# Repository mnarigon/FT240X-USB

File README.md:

## An FT240X-based parallel to USB converter

===== Description =====

This is an FT240X-based parallel to USB converter intended as an option for John Monahan's S-100 bus computer boards.

NOTE: These are the prototype files and I have not yet built and tested the prototype. I plan to update these files when that is complete. Quantity 5 boards was roughly $12 with tax and two-week shipping. Parts for 5 boards was roughly $50 with tax and one week shipping.

===== Design Files =====

The design files are in KiCad 10. The board fabrication parameters are 1.6mm, 2-layer, with 1 oz copper. There is a BOM in the documents folder.

===== Assembly Steps =====

  - Tin all the solder pads with the appropriate amount of solder.
  - Mount the front and back passives.
  - Mount the 24-SSOP transceiver.
  - Replace pins 1 and 9 on each 9-pin SMD connector header with pins from the THT connector header.
  - Mount the connector headers.
  - Mount the mini-USB connector.

The FT240X requires programming to enable the PWREN# functionality. For use in John's boards this is not required since John's designs do not use PWREN# and by default the signal is tri-stated.

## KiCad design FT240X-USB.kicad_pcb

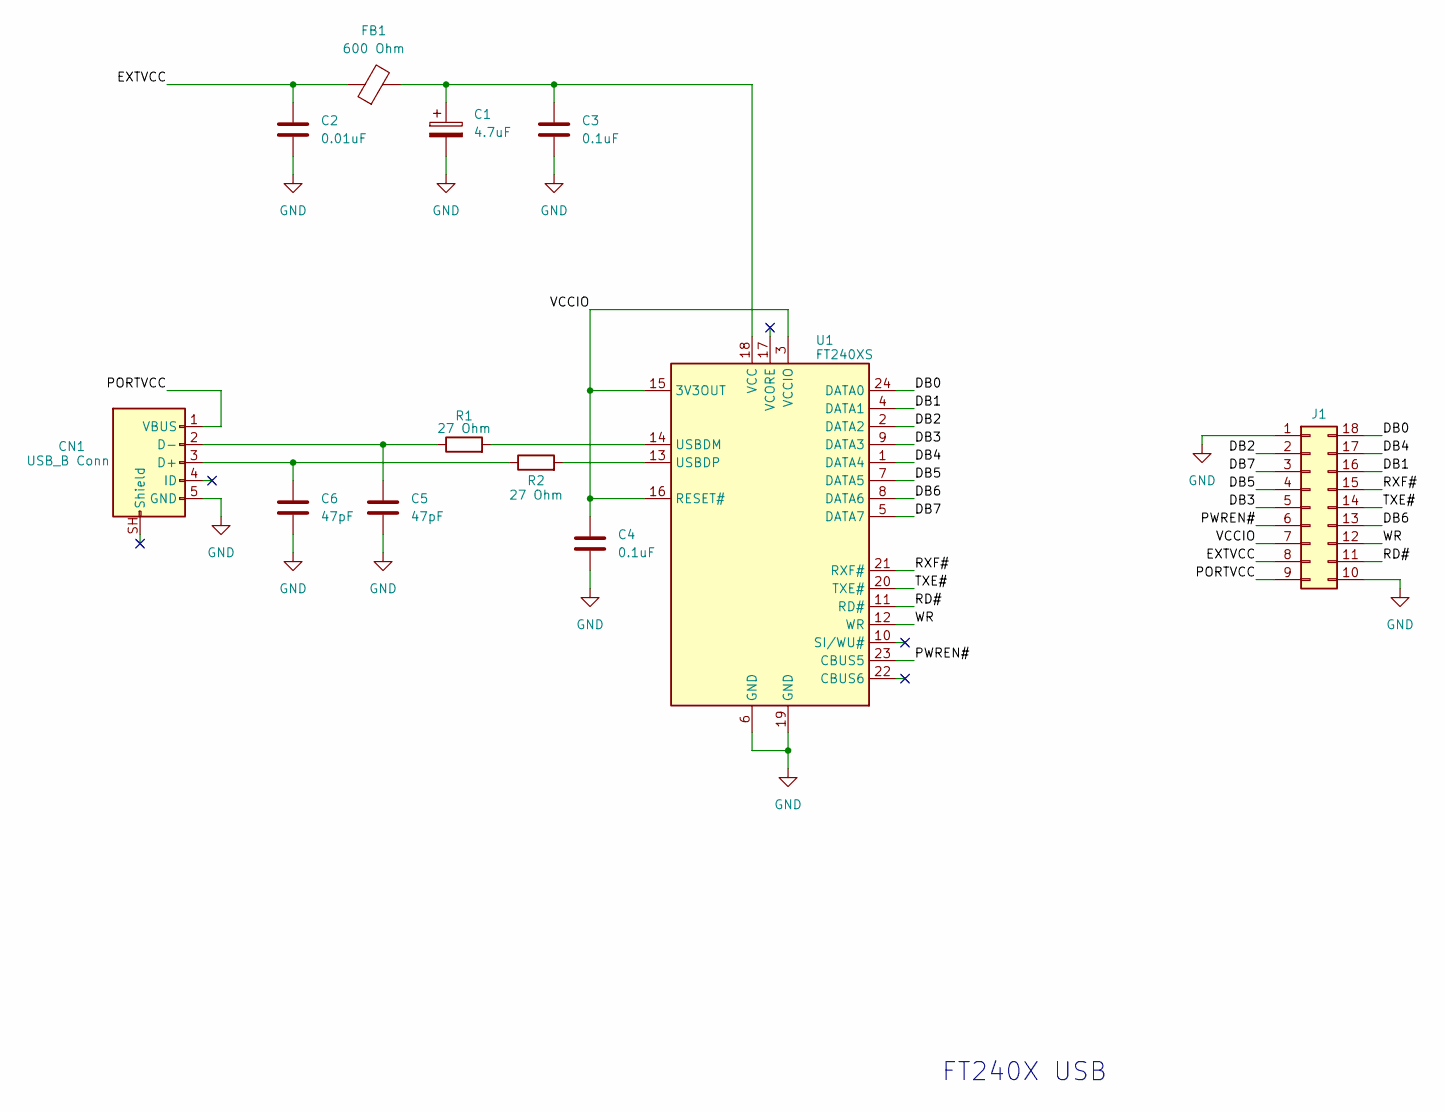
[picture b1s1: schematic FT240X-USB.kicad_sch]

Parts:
C1: 4.7uF; C_0805_2012Metric
C2: 0.01uF; C_0402_1005Metric
C3, C4: 0.1uF; C_0402_1005Metric
C5, C6: 47pF; C_0402_1005Metric
CN1: USB_B Conn; USB_Mini-B_TE_1734035_Horizontal
FB1: 600 Ohm; L_0805_2012Metric
J1: CustomPinHeader_02x09_P2.54mm_Hybrid
R1, R2: 27 Ohm; R_0402_1005Metric
U1: FT240XS; SSOP-24_3.9x8.7mm_P0.635mm

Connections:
/DB0: J1.18, U1.24 (DATA0)
/DB1: J1.16, U1.4 (DATA1)
/DB2: J1.2, U1.2 (DATA2)
/DB3: J1.5, U1.9 (DATA3)
/DB4: J1.17, U1.1 (DATA4)
/DB5: J1.4, U1.7 (DATA5)
/DB6: J1.13, U1.8 (DATA6)
/DB7: J1.3, U1.5 (DATA7)
/EXTVCC: C2.1, FB1.1, J1.8
/PORTVCC: CN1.1 (VBUS), J1.9
/PWREN#: J1.6, U1.23 (CBUS5)
/RD#: J1.11, U1.11 (RD#)
/RXF#: J1.15, U1.21 (RXF#)
/TXE#: J1.14, U1.20 (TXE#)
/VCCIO: C4.1, J1.7, U1.3 (VCCIO), U1.15 (3V3OUT), U1.16 (RESET#)
/WR: J1.12, U1.12 (WR)
GND: C1.2, C2.2, C3.2, C4.2, C5.2, C6.2, CN1.5 (GND), J1.1, J1.10, U1.6 (GND), U1.19 (GND)
unnamed: C6.1, CN1.3 (D+), R2.1
unnamed: C5.1, CN1.2 (D-), R1.1
unnamed: R1.2, U1.14 (USBDM)
unnamed: R2.2, U1.13 (USBDP)
unnamed: C1.1, C3.1, FB1.2, U1.18 (VCC)

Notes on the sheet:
FT240X USB

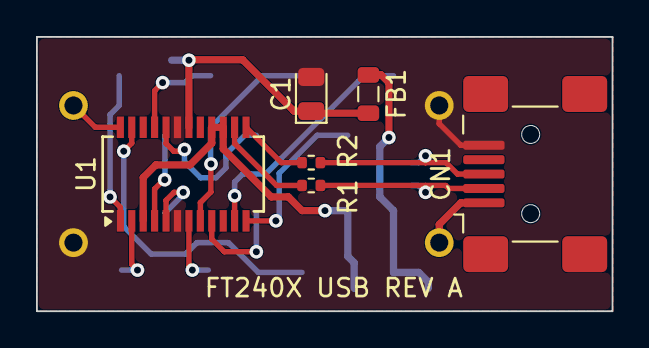
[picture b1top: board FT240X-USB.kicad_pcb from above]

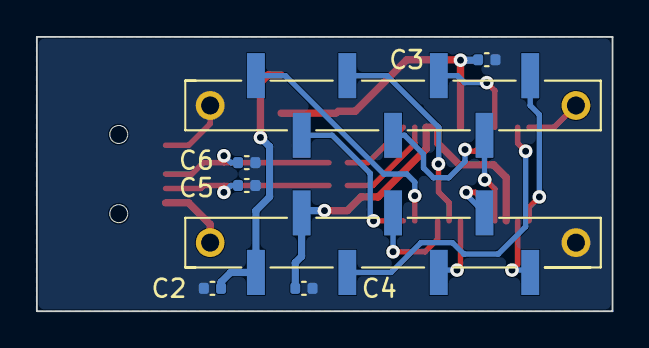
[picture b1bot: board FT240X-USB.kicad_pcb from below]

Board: 2 copper layers, 32.0 x 15.2 mm, 12 parts (6 on the bottom side), 22 nets.
